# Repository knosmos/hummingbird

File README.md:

<picture>
  <source media="(prefers-color-scheme: dark)" srcset="https://github.com/user-attachments/assets/7356b551-4785-46c3-8079-baab0482c5df">
  <source media="(prefers-color-scheme: light)" srcset="https://github.com/user-attachments/assets/484456df-929e-4e9f-abab-7f0c61837f22">
  
</picture>

Custom STM32 flight controller for MIT Design Build Fly 2025

### Features

- STM32F103C8T6 microprocessor
- Altimeter and IMU
- 2x Servo PWM
- 12V / 5V LDO regulators
- MOSFET LED drive circuits
- Hall effect sensor input
- GPS and magnetometer input

### Layout

### Schematic

### Renderings

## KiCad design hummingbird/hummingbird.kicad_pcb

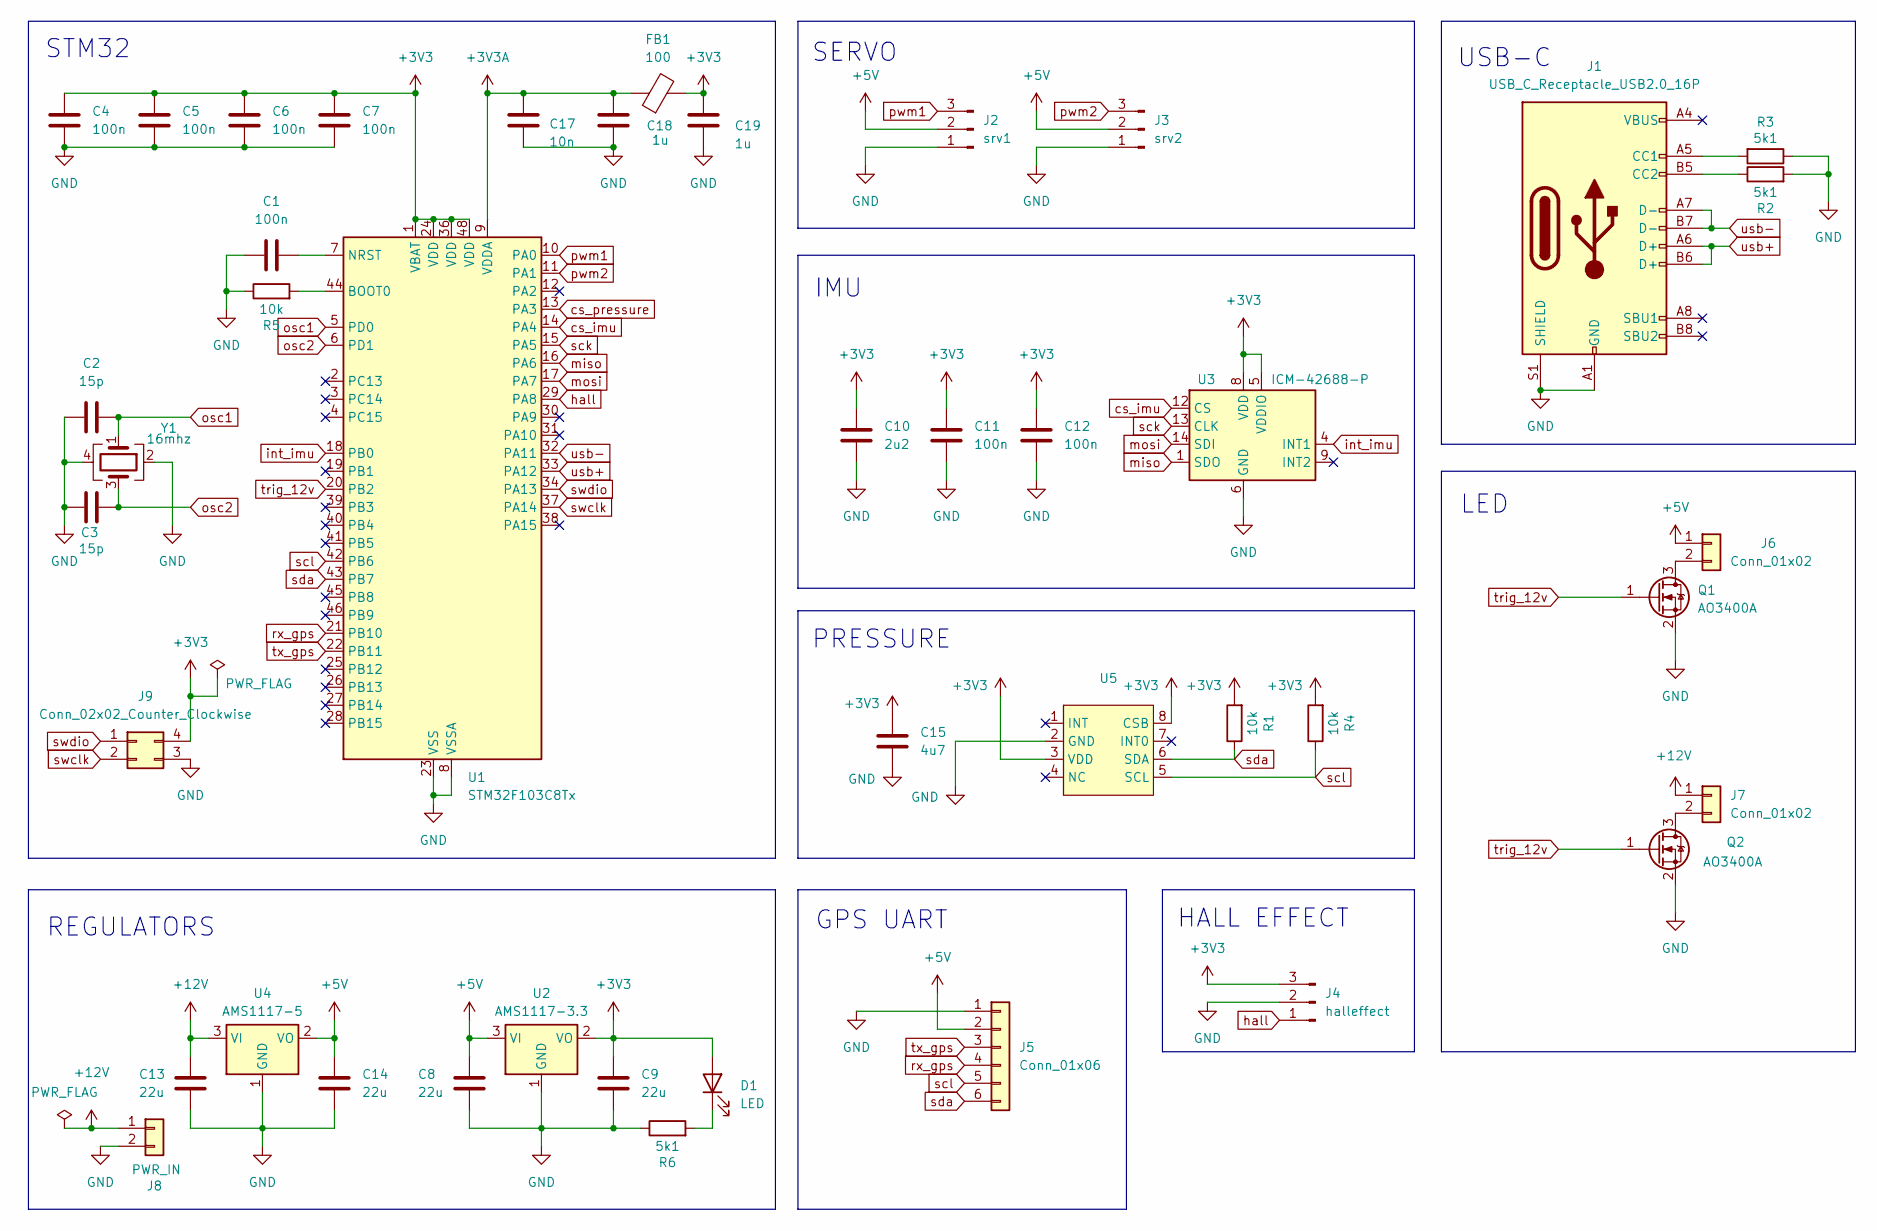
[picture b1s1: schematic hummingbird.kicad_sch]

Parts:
C1, C4, C5, C6, C7, C11, C12: 100n; C_0402_1005Metric; LCSC C1525
C2, C3: 15p; C_0402_1005Metric; LCSC C1548
C8, C13: 22u; C_0805_2012Metric; LCSC C45783
C9, C14: 22u; C_0603_1608Metric; LCSC C59461
C10: 2u2; C_0402_1005Metric; LCSC C12530
C15: 4u7; C_0402_1005Metric; LCSC C23733
C17: 10n; C_0402_1005Metric; LCSC C15195
C18, C19: 1u; C_0402_1005Metric; LCSC C52923
D1: LED; LED_0603_1608Metric; LCSC C2286
FB1: 100; L_0805_2012Metric; LCSC C1015
J1: USB_C_Receptacle_USB2.0_16P; USB_C_Receptacle_GCT_USB4105-xx-A_16P_TopMnt_Horizontal; LCSC C2765186
J2: srv1; PinHeader_1x03_P2.54mm_Horizontal
J3: srv2; PinHeader_1x03_P2.54mm_Horizontal
J4: halleffect; PinHeader_1x03_P2.54mm_Horizontal
J5: Conn_01x06; JST_SH_SM06B-SRSS-TB_1x06-1MP_P1.00mm_Horizontal
J6, J7: Conn_01x02; SolderWire-0.1sqmm_1x02_P3.6mm_D0.4mm_OD1mm
J8: PWR_IN; PinHeader_2x01_P2.54mm_Vertical
J9: Conn_02x02_Counter_Clockwise; PinHeader_2x02_P2.54mm_Vertical
Q1, Q2: AO3400A; SOT-23; LCSC C20917
R1, R4, R5: 10k; R_0402_1005Metric; LCSC C25744
R2, R3, R6: 5k1; R_0402_1005Metric; LCSC C25905
U1: STM32F103C8Tx; LQFP-48_7x7mm_P0.5mm
U2: AMS1117-3.3; SOT-223-3_TabPin2; LCSC C6186
U3: ICM-42688-P; LGA-14_3x2.5mm_P0.5mm_LayoutBorder3x4y; LCSC C1850418
U4: AMS1117-5; SOT-223-3_TabPin2; LCSC C6187
U5: QFN (3.8x3.8); LCSC C138665
Y1: 16mhz; Crystal_SMD_3225-4Pin_3.2x2.5mm; LCSC C13738

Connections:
+3V3: C4.2, C5.2, C6.2, C7.2, C9.1, C10.1, C11.1, C12.1, C15.1, C19.1, D1.2 (A), FB1.2, J4.3, J9.4, R1.2, R4.2, U1.1 (VBAT), U1.24 (VDD), U1.36 (VDD), U1.48 (VDD), U2.2 (VO), U3.5 (VDDIO), U3.8 (VDD), U5.3 (VDD), U5.8 (CSB)
+3V3A: C17.1, C18.1, FB1.1, U1.9 (VDDA)
+5V: C8.1, C14.1, J2.2, J3.2, J5.2, J6.1, U2.3 (VI), U4.2 (VO)
+12V: C13.1, J7.1, J8.1, U4.3 (VI)
GND: C1.1, C2.1, C3.1, C4.1, C5.1, C6.1, C7.1, C8.2, C9.2, C10.2, C11.2, C12.2, C13.2, C14.2, C15.2, C17.2, C18.2, C19.2, J1.A1 (GND), J1.A12 (GND), J1.B1 (GND), J1.B12 (GND), J1.S1 (SHIELD), J2.1, J3.1, J4.2, J5.1, J8.2, J9.3, Q1.2 (S), Q2.2 (S), R2.2, R3.1, R5.1, R6.1, U1.8 (VSSA), U1.23 (VSS), U1.35 (VSS), U1.47 (VSS), U2.1 (GND), U3.6 (GND), U3.7 (RESV), U3.11 (RESV), U4.1 (GND), U5.2 (GND), Y1.2, Y1.4
unnamed: D1.1 (K), R6.2
unnamed: J1.A5 (CC1), R3.2
unnamed: J1.B5 (CC2), R2.1
unnamed: J6.2, Q1.3 (D)
unnamed: J7.2, Q2.3 (D)
unnamed: R5.2, U1.44 (BOOT0)
unnamed: C1.2, U1.7 (NRST)
cs_imu: U1.14 (PA4), U3.12 (CS)
cs_pressure: U1.13 (PA3)
hall: J4.1, U1.29 (PA8)
int_imu: U1.18 (PB0), U3.4 (INT1)
miso: U1.16 (PA6), U3.1 (SDO)
mosi: U1.17 (PA7), U3.14 (SDI)
osc1: C2.2, U1.5 (PD0), Y1.1
osc2: C3.2, U1.6 (PD1), Y1.3
pwm1: J2.3, U1.10 (PA0)
pwm2: J3.3, U1.11 (PA1)
rx_gps: J5.4, U1.21 (PB10)
sck: U1.15 (PA5), U3.13 (CLK)
scl: J5.5, R4.1, U1.42 (PB6), U5.5 (SCL)
sda: J5.6, R1.1, U1.43 (PB7), U5.6 (SDA)
swclk: J9.2, U1.37 (PA14)
swdio: J9.1, U1.34 (PA13)
trig_12v: Q1.1 (G), Q2.1 (G), U1.20 (PB2)
tx_gps: J5.3, U1.22 (PB11)
usb+: J1.A6 (D+), J1.B6 (D+), U1.33 (PA12)
usb-: J1.A7 (D-), J1.B7 (D-), U1.32 (PA11)

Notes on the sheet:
LED
HALL EFFECT
REGULATORS
USB-C
SERVO
IMU
PRESSURE
STM32
GPS UART

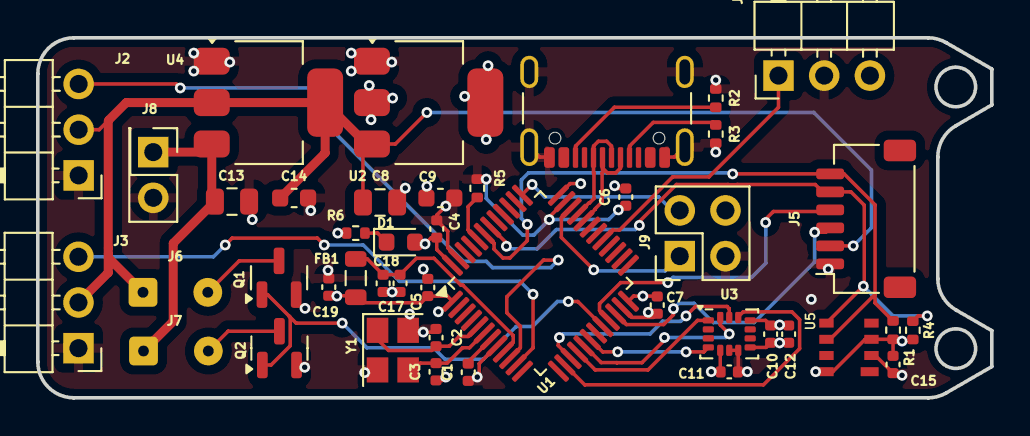
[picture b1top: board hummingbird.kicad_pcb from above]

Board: 4 copper layers, 53.0 x 20.0 mm, 43 parts (0 on the bottom side), 31 nets.

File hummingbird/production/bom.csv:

Designator,Footprint,Quantity,Value,LCSC Part #
"C1, C11, C12, C4, C5, C6, C7",0402,7,100n,C1525
C10,0402,1,2u2,C12530
"C13, C8",0805,2,22u,C45783
"C14, C9",0603,2,22u,C59461
C15,0402,1,4u7, C23733
C17,0402,1,10n,C15195
"C18, C19",0402,2,1u,C52923
"C2, C3",0402,2,15p,C1548
D1,0603,1,LED,C2286
FB1,0805,1,100,C1015
J1,USB_C_Receptacle_GCT_USB4105-xx-A_16P_TopMnt_Horizontal,1,USB_C_Receptacle_USB2.0_16P,C2765186
J2,PinHeader_1x03_P2.54mm_Horizontal,1,srv1,
J3,PinHeader_1x03_P2.54mm_Horizontal,1,srv2,
J4,PinHeader_1x03_P2.54mm_Horizontal,1,halleffect,
J5,JST_SH_SM06B-SRSS-TB_1x06-1MP_P1.00mm_Horizontal,1,Conn_01x06,C3029345
"J6, J7",SolderWire-0.1sqmm_1x02_P3.6mm_D0.4mm_OD1mm,2,Conn_01x02,
J8,PinHeader_2x01_P2.54mm_Vertical,1,PWR_IN,
J9,PinHeader_2x02_P2.54mm_Vertical,1,Conn_02x02_Counter_Clockwise,
"Q1, Q2",SOT-23,2,AO3400A,C20917
"R1, R4, R5",0402,3,10k,C25744
"R2, R3, R6",0402,3,5k1,C25905
U1,LQFP-48_7x7mm_P0.5mm,1,STM32F103C8Tx,
U2,SOT-223-3_TabPin2,1,AMS1117-3.3,C6186
U3,LGA-14_3x2.5mm_P0.5mm_LayoutBorder3x4y,1,ICM-42688-P,C1850418
U4,SOT-223-3_TabPin2,1,AMS1117-5,C6187
U5,QFN (3.8x3.8),1,~,C138665
Y1,Crystal_SMD_3225-4Pin_3.2x2.5mm,1,16mhz,C13738

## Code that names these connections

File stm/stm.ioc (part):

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Mcu.Name=STM32F103C(8-B)Tx
Mcu.Package=LQFP48
Mcu.UserName=STM32F103C8Tx
PA0-WKUP.Signal=S_TIM2_CH1_ETR
PA11.Mode=Device
PA11.Signal=USB_DM
PA12.Mode=Device
PA12.Signal=USB_DP
PA13.Signal=SYS_JTMS-SWDIO
PA14.Signal=SYS_JTCK-SWCLK
PA3.Signal=GPIO_Output
PA4.Signal=GPIO_Output
PA5.Signal=SPI1_SCK
PA6.Signal=SPI1_MISO
PA7.Signal=SPI1_MOSI
PA8.Signal=GPIO_Input
PB10.Signal=USART3_TX
PB11.Signal=USART3_RX
PB2.Signal=GPIO_Output
PB6.Signal=I2C1_SCL
PB7.Signal=I2C1_SDA
PD0-OSC_IN.Mode=HSE-External-Oscillator
PD0-OSC_IN.Signal=RCC_OSC_IN
PD1-OSC_OUT.Mode=HSE-External-Oscillator
PD1-OSC_OUT.Signal=RCC_OSC_OUT
RCC.SYSCLKFreq_VALUE=48000000
RCC.SYSCLKSource=RCC_SYSCLKSOURCE_PLLCLK
board=custom

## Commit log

2025-02-24 backup before replacing sensor
2025-02-24 completion, may have usbc placement bug
2025-03-22 Add STM32 skeleton code
